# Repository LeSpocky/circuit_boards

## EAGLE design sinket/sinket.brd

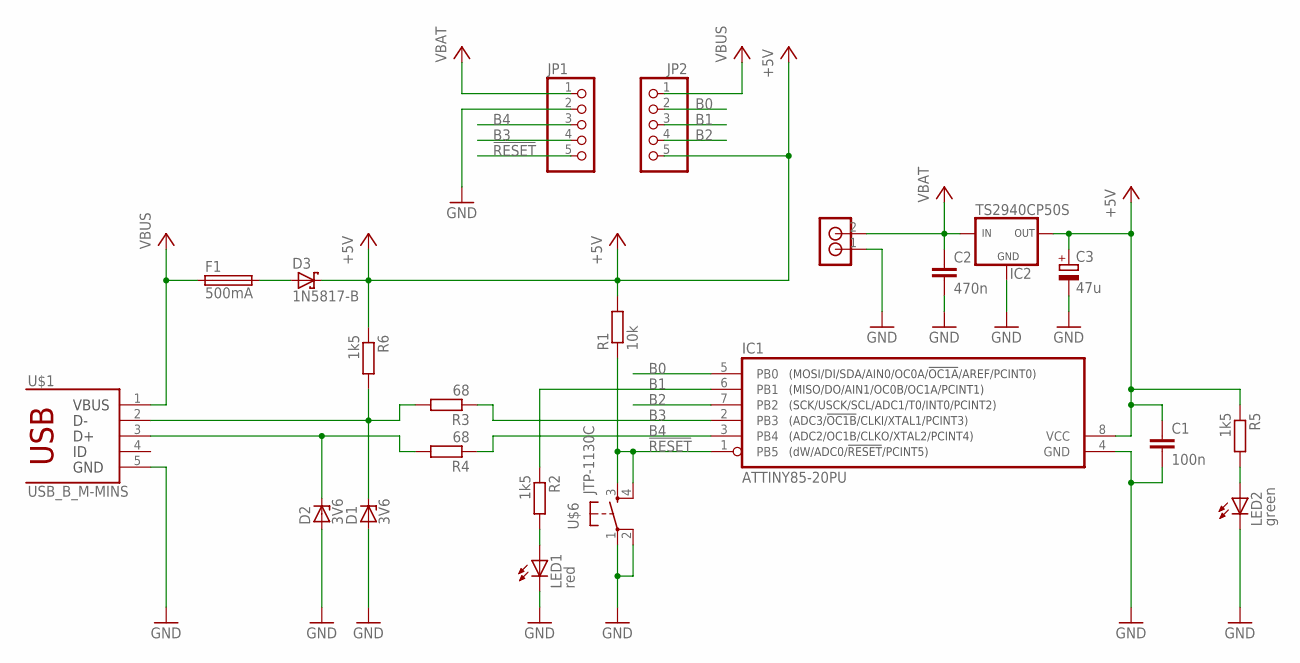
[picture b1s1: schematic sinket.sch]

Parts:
C1: 100n; C1206
C2: 470n; C050-025X075
C3: 47u; E2,5-6
D1, D2: 3V6; SOD80C
D3: 1N5817-B; DO41-7.6
F1: 500mA; LP60-050
IC1: ATTINY85-20PU; 8P3
IC2: TS2940CP50S; TO-252
JP1, JP2: PINHD-1X5; 1X05
LED1: red; LED5MM
LED2: green; LED5MM
R1: 10k; R1206
R2, R5, R6: 1k5; R1206
R3, R4: 68; R1206
U$1: USB_B_M-MINS; LUMBERG_2486-01
U$6: JTP-1130C; JTP-1130
U$7: RIACON_101_2

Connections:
!RESET: IC1.1 (PB5), JP1.5, R1.1, U$6.3 (S), U$6.4 (S1)
+5V: C1.1, C3.+, D3.C, IC1.8 (VCC), IC2.3 (OUT), JP2.5, R1.2, R5.1, R6.1
B0: IC1.5 (PB0), JP2.2
B1: IC1.6 (PB1), JP2.3, R2.1
B2: IC1.7 (PB2), JP2.4
B3: IC1.2 (PB3), JP1.4, R3.1
B4: IC1.3 (PB4), JP1.3, R4.1
GND: C1.2, C2.2, C3.-, D1.A, D2.A, IC1.4 (GND), IC2.2 (GND), JP1.2, LED1.K (C), LED2.K (C), U$1.5, U$6.1, U$6.2 (P1), U$7.1
unnamed: D1.C, R3.2, R6.2, U$1.2
unnamed: D3.A, F1.P$2 (2)
unnamed: D2.C, R4.2, U$1.3
unnamed: LED1.A, R2.2
unnamed: LED2.A, R5.2
VBAT: C2.1, IC2.1 (IN), JP1.1, U$7.2
VBUS: F1.P$1 (1), JP2.1, U$1.1

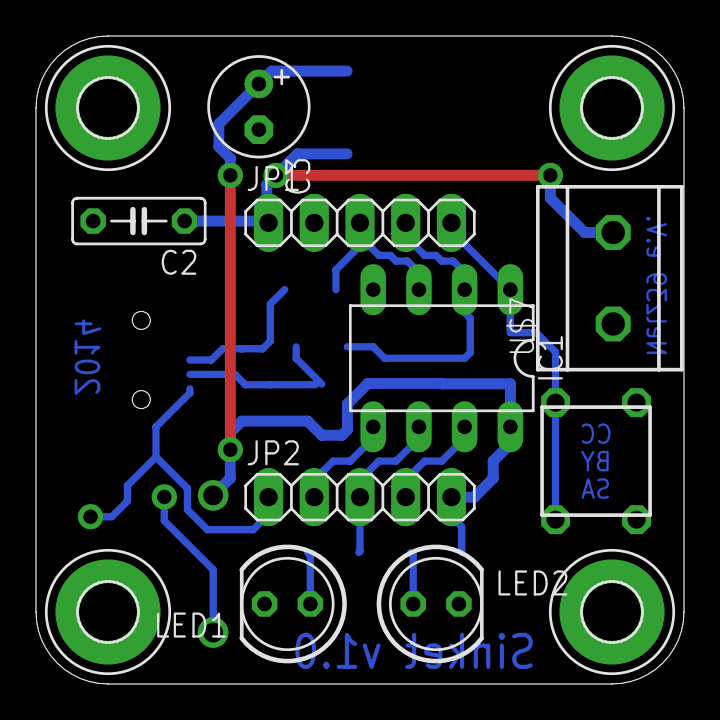
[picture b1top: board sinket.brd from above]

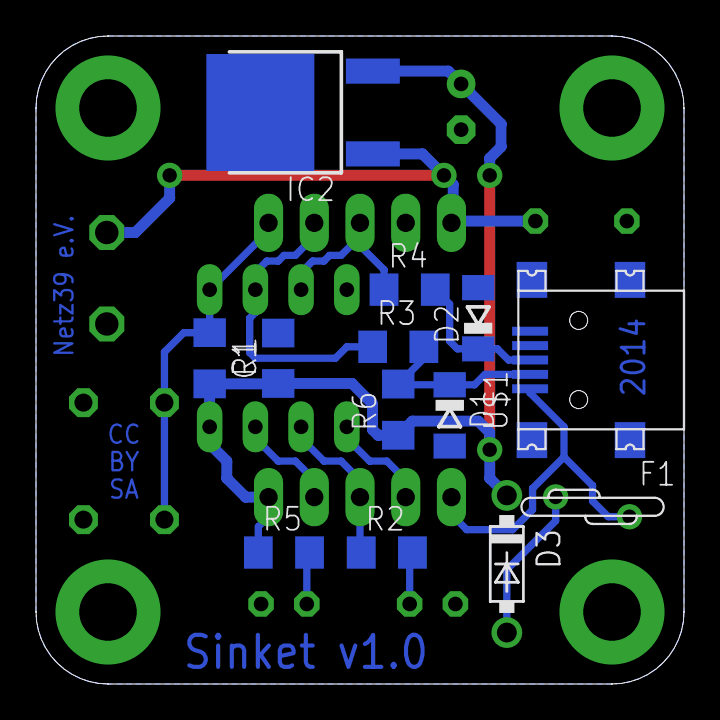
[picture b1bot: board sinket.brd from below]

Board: 2 copper layers, 36.0 x 36.0 mm, 26 parts (13 on the bottom side), 15 nets.

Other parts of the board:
U$2, U$3, U$4, U$5: 3,2-PAD

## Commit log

2015-11-28 change capacity package
    the former one was probably unrealstic for the desired value
